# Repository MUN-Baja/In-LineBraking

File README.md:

# In-LineBraking
In-Line Braking Circuit used for agility test purposes

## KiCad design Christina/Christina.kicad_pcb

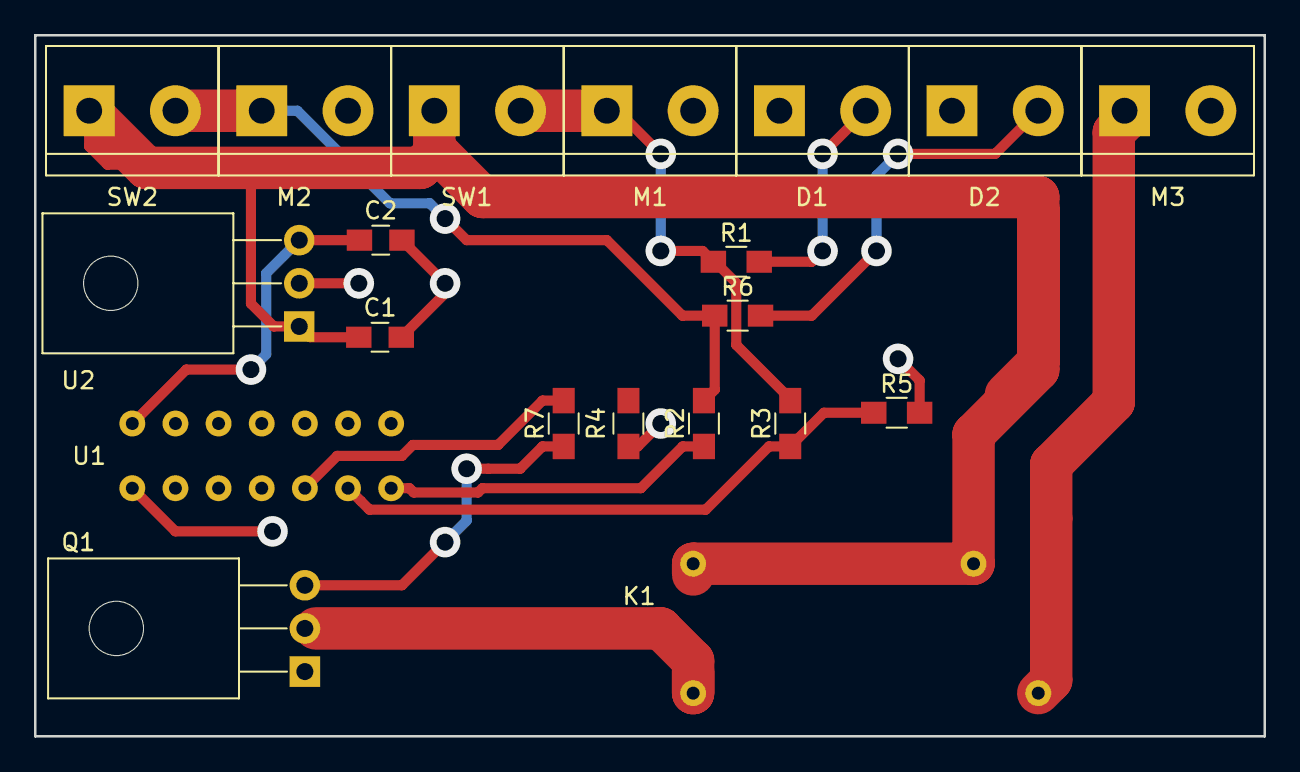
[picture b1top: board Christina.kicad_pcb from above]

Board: 2 copper layers, 72.4 x 41.3 mm, 20 parts (0 on the bottom side), 11 nets.

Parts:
C1, C2: C; C_0805_HandSoldering
D1, D2: LED; TerminalBlock_bornier-2_P5.08mm
K1: FINDER-32.21-x300; SPSTRELAYPANASONIC
M1, M2, M3: Motor_DC; TerminalBlock_bornier-2_P5.08mm
Q1: BD139; TO-126_Horizontal
R1, R2, R3, R4, R5, R6, R7: R; R_0805_HandSoldering
SW1, SW2: SW_Push; TerminalBlock_bornier-2_P5.08mm
U1: 74LS386; XORGATE
U2: L7805; TO-126_Horizontal

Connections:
+12V: C1.1, SW1.1, SW2.1, U2.1
GND: C1.2, C2.2, D1.1, D2.1, M1.2, M2.2, M3.2, Q1.1, R4.2, R5.2, U1.7, U2.2
unnamed: D1.2, R1.2
unnamed: D2.2, R6.2
unnamed: M1.1, R1.1, R3.2, SW1.2
unnamed: M2.1, R2.2, R6.1, SW2.2
unnamed: Q1.3, R7.1
unnamed: R2.1, U1.1
unnamed: R3.1, R5.1, U1.2
unnamed: R7.2, U1.3
Vcc: C2.1, U1.14, U2.3

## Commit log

2018-04-24 PCB Prelim Work For In-Line Braking Circuit
    PCB Prelim Work For In-Line Braking Circuit
2018-04-27 PCB Footprints added
2018-04-30 Braking PCB Rev1
2018-05-06 uploaded rerouted board
2018-05-11 fixed routing, schematic issue
